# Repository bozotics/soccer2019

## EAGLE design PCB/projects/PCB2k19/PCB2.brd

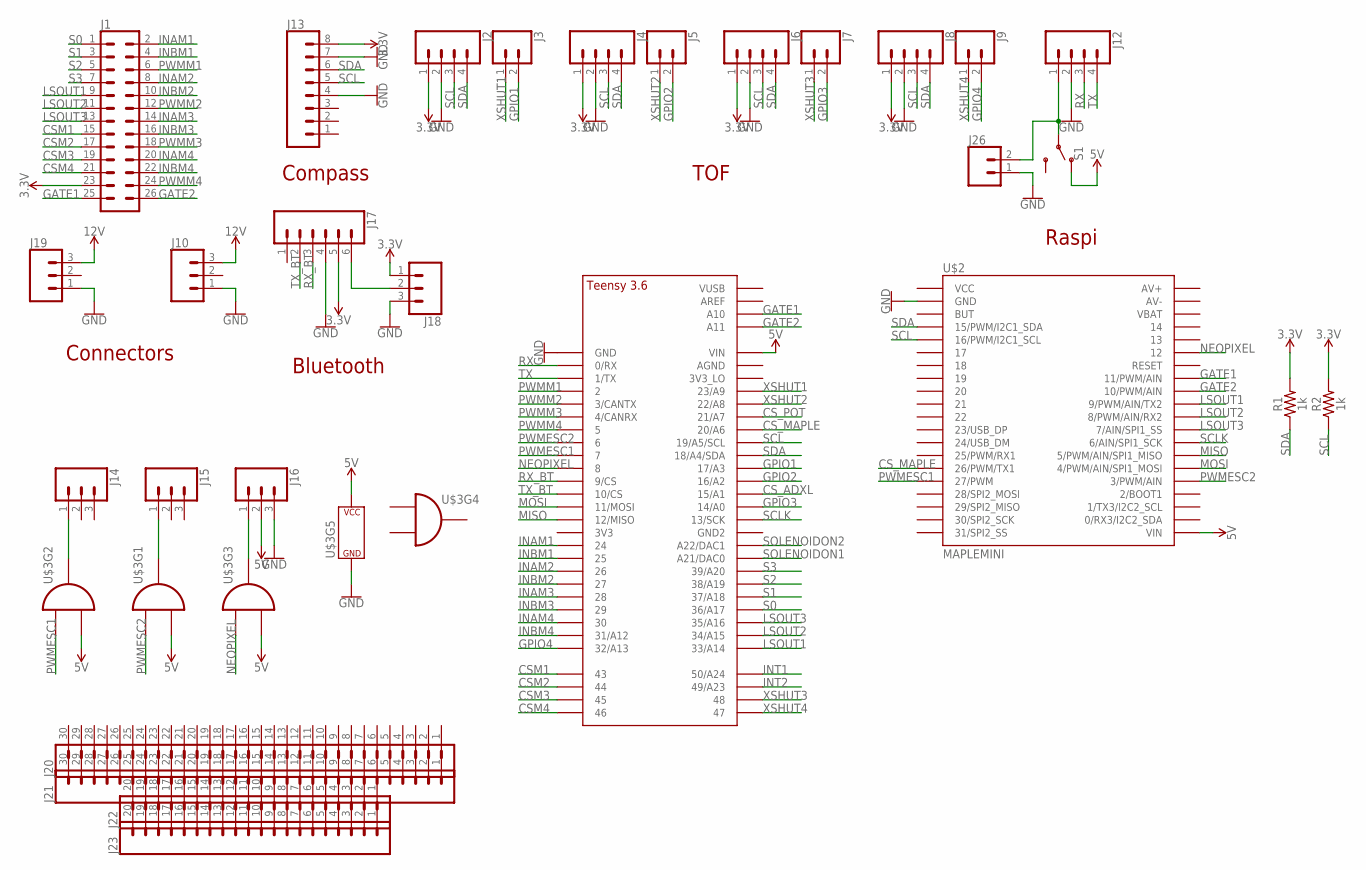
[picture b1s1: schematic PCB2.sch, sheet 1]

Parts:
J1: CONN_13X22X13; 2X13
J2, J4, J6, J8, J12: CONN_04LOCK; 1X04_LOCK
J3, J5, J7, J9, J26: CONN_02LOCK; 1X02_LOCK
J10, J19: CONN_03-SCREW-5MM; SCREWTERMINAL-5MM-3
J13: CONN_08LOCK; 1X08_LOCK
J14, J15, J16, J18: CONN_03LOCK; 1X03_LOCK
J17: CONN_06LOCK; 1X06_LOCK
J20, J21: CONN_30; 1X30
J22, J23: CONN_20; 1X20
R1, R2: 1k; 0603
S1: SWITCH-SPDT-PTH-11.6X4.0MM-LOCK; SWITCH_SPDT_PTH_11.6X4.0MM_LOCK
U$1: TEENSY_3.5/3.6_BASIC
U$2: MAPLEMINI; 20-DIP
U$3: 74HCT08; SOIC-14

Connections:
3.3V: J1.23, J2.1, J4.1, J6.1, J8.1, J13.8, J17.5, J18.1, R1.2, R2.2; also elsewhere on the board
5V: J16.2, S1.1 (O), U$1.VIN, U$2.21 (VIN), U$3.P2 (I1), U$3.P5 (I1), U$3.P10 (I1), U$3.P14 (P$V+); also elsewhere on the board
12V: J10.3, J19.3; also elsewhere on the board
CSM1: J1.15, U$1.43
CSM2: J1.17, U$1.44
CSM3: J1.19, U$1.45
CSM4: J1.21, U$1.46
CS_ADXL: U$1.15/A1; also elsewhere on the board
CS_MAPLE: U$1.20/A6, U$2.15 (26/PWM/TX1)
CS_POT: U$1.21/A7; also elsewhere on the board
GATE1: J1.25, U$1.A10, U$2.33 (11/PWM/AIN)
GATE2: J1.26, U$1.A11, U$2.32 (10/PWM/AIN)
GND: J2.2, J4.2, J6.2, J8.2, J10.1, J12.2, J13.4, J13.7, J16.3, J17.4, J18.3, J19.1, J26.1, U$1.GND, U$2.2 (GND), U$3.P7 (P$V-); also elsewhere on the board
GPIO1: J3.2, U$1.17/A3
GPIO2: J5.2, U$1.16/A2
GPIO3: J7.2, U$1.14/A0
GPIO4: J9.2, U$1.32/A13
INAM1: J1.2, U$1.24
INAM2: J1.8, U$1.26
INAM3: J1.14, U$1.28
INAM4: J1.20, U$1.30
INBM1: J1.4, U$1.25
INBM2: J1.10, U$1.27
INBM3: J1.16, U$1.29
INBM4: J1.22, U$1.31/A12
INT1: U$1.50/A24; also elsewhere on the board
INT2: U$1.49/A23; also elsewhere on the board
LSOUT1: J1.9, U$1.33/A14, U$2.31 (9/PWM/AIN/TX2)
LSOUT2: J1.11, U$1.34/A15, U$2.30 (8/PWM/AIN/RX2)
LSOUT3: J1.13, U$1.35/A16, U$2.29 (7/AIN/SPI1_SS)
MISO: U$1.12/MISO, U$2.27 (5/PWM/AIN/SPI1_MISO); also elsewhere on the board
MOSI: U$1.11/MOSI, U$2.26 (4/PWM/AIN/SPI1_MOSI); also elsewhere on the board
unnamed: J12.1, J26.2, S1.2
unnamed: J16.1, U$3.P8 (O)
unnamed: J14.1, U$3.P6 (O)
unnamed: J15.1, U$3.P3 (O)
unnamed: J17.6, J18.2
NEOPIXEL: U$1.8, U$2.35 (12), U$3.P9 (I0)
PWMESC1: U$1.7, U$2.16 (27/PWM), U$3.P4 (I0)
PWMESC2: U$1.6, U$2.25 (3/PWM/AIN), U$3.P1 (I0)
PWMM1: J1.6, U$1.2
PWMM2: J1.12, U$1.3/CANTX
PWMM3: J1.18, U$1.4/CANRX
PWMM4: J1.24, U$1.5
RX: J12.3, U$1.0/RX
RX_BT: J17.3, U$1.9/CS
S0: J1.1, U$1.36/A17
S1: J1.3, U$1.37/A18
S2: J1.5, U$1.38/A19
S3: J1.7, U$1.39/A20
SCL: J2.3, J4.3, J6.3, J8.3, J13.5, R2.1, U$1.19/A5/SCL, U$2.5 (16/PWM/I2C1_SCL)
SCLK: U$1.13/SCK, U$2.28 (6/AIN/SPI1_SCK); also elsewhere on the board
SDA: J2.4, J4.4, J6.4, J8.4, J13.6, R1.1, U$1.18/A4/SDA, U$2.4 (15/PWM/I2C1_SDA)
SOLENOIDON1: U$1.21/DAC0 (A21/DAC0); also elsewhere on the board
SOLENOIDON2: U$1.A22/DAC1; also elsewhere on the board
TX: J12.4, U$1.1/TX
TX_BT: J17.2, U$1.10/CS
XSHUT1: J3.1, U$1.23/A9
XSHUT2: J5.1, U$1.22/A8
XSHUT3: J7.1, U$1.48
XSHUT4: J9.1, U$1.47

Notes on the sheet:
Raspi
TOF
Compass
Connectors
Bluetooth

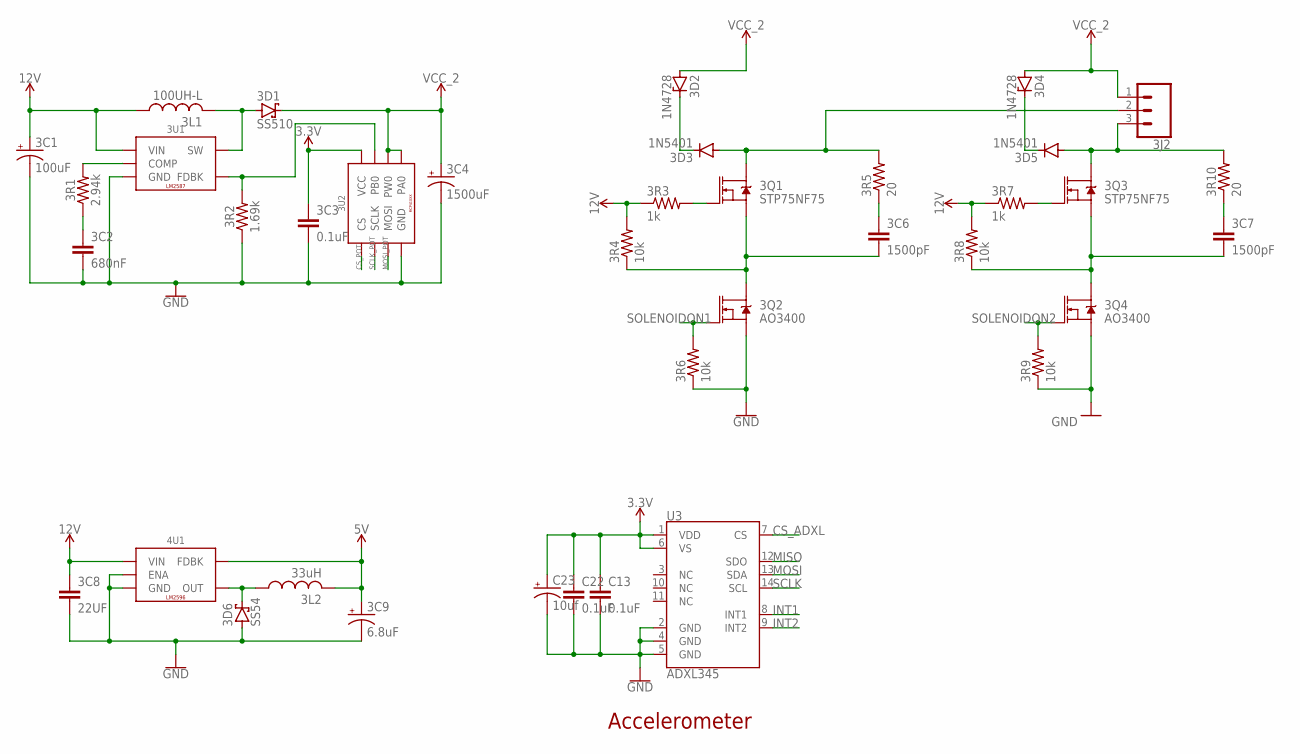
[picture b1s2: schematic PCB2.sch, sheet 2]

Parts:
3C1: 100uF; PANASONIC_D
3C2: 680nF; 0603
3C3: 0.1uF; 0603
3C4: 1500uF; 1000UF-CAP
3C6, 3C7: 1500pF; 0603
3C8: 22UF; 1210
3C9: 6.8uF; A/3216-18R
3D1: SS510; SMB
3D2, 3D4: 1N4728; DO41Z10
3D3, 3D5: 1N5401; DO201-15
3D6: SS54; SMB
3J2: CONN_03-SCREW-5MM; SCREWTERMINAL-5MM-3
3L1: 100UH-L
3L2: 33uH; 127
3Q1, 3Q3: STP75NF75; TO220V
3Q2, 3Q4: AO3400; SOT23-3
3R1: 2.94k; 0603
3R2: 1.69k; 0603
3R3, 3R7: 1k; 0603
3R4, 3R6, 3R8, 3R9: 10k; 0603
3R5, 3R10: 20; 0603
3U1: LM2587; TO-263
3U2: MCP41XXX; SOIC-8
4U1: LM2596; TO-263
C13, C22: 0.1uF; 0603
C23: 10uf; R/2012-12R
U3: ADXL345; LGA-14

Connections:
3.3V: 3C3.1, 3U2.8 (VCC), C13.1, C22.1, C23.+, U3.1 (VDD), U3.6 (VS); also elsewhere on the board
5V: 3C9.+, 3L2.2, 4U1.P4 (FDBK); also elsewhere on the board
12V: 3C1.+, 3C8.1, 3L1.P1 (1), 3R3.1, 3R4.2, 3R7.1, 3R8.2, 3U1.P5 (VIN), 4U1.P1 (VIN); also elsewhere on the board
CS_ADXL: U3.7 (CS); also elsewhere on the board
CS_POT: 3U2.1 (CS); also elsewhere on the board
GND: 3C1.-, 3C2.2, 3C3.2, 3C4.-, 3C8.2, 3C9.-, 3D6.A, 3Q2.2 (S), 3Q4.2 (S), 3R2.1, 3R6.1, 3R9.1, 3U1.P3 (GND), 3U2.4 (GND), 4U1.P3 (GND), 4U1.P5 (ENA), 4U1.TAB (GND), C13.2, C22.2, C23.-, U3.2 (GND), U3.4 (GND), U3.5 (GND); also elsewhere on the board
INT1: U3.8 (INT1); also elsewhere on the board
INT2: U3.9 (INT2); also elsewhere on the board
MISO: U3.12 (SDO); also elsewhere on the board
MOSI: U3.13 (SDA); also elsewhere on the board
MOSI_POT: 3U2.3 (MOSI)
unnamed: 3D1.A, 3L1.P2 (2), 3U1.P4 (SW)
unnamed: 3C6.2, 3Q1.3 (S), 3Q2.3 (D), 3R4.1
unnamed: 3R1.2, 3U1.P1 (COMP)
unnamed: 3C2.1, 3R1.1
unnamed: 3Q1.1 (G), 3R3.2
unnamed: 3D2.C, 3D3.C
unnamed: 3C6.1, 3R5.1
unnamed: 3C7.2, 3Q3.3 (S), 3Q4.3 (D), 3R8.1
unnamed: 3Q3.1 (G), 3R7.2
unnamed: 3D4.C, 3D5.C
unnamed: 3C7.1, 3R10.1
unnamed: 3D6.C, 3L2.1, 4U1.P2 (OUT)
unnamed: 3R2.2, 3U1.P2 (FDBK), 3U2.7 (PB0)
SCLK: U3.14 (SCL); also elsewhere on the board
SCLK_POT: 3U2.2 (SCLK)
SOLENOID-: 3D3.A, 3J2.2, 3Q1.2 (D), 3R5.2
SOLENOID-1: 3D5.A, 3J2.3, 3Q3.2 (D), 3R10.2
SOLENOIDON1: 3Q2.1 (G), 3R6.2; also elsewhere on the board
SOLENOIDON2: 3Q4.1 (G), 3R9.2; also elsewhere on the board
VCC_2: 3C4.+, 3D1.C, 3D2.A, 3D4.A, 3J2.1, 3U2.5 (PA0), 3U2.6 (PW0)

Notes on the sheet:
Accelerometer

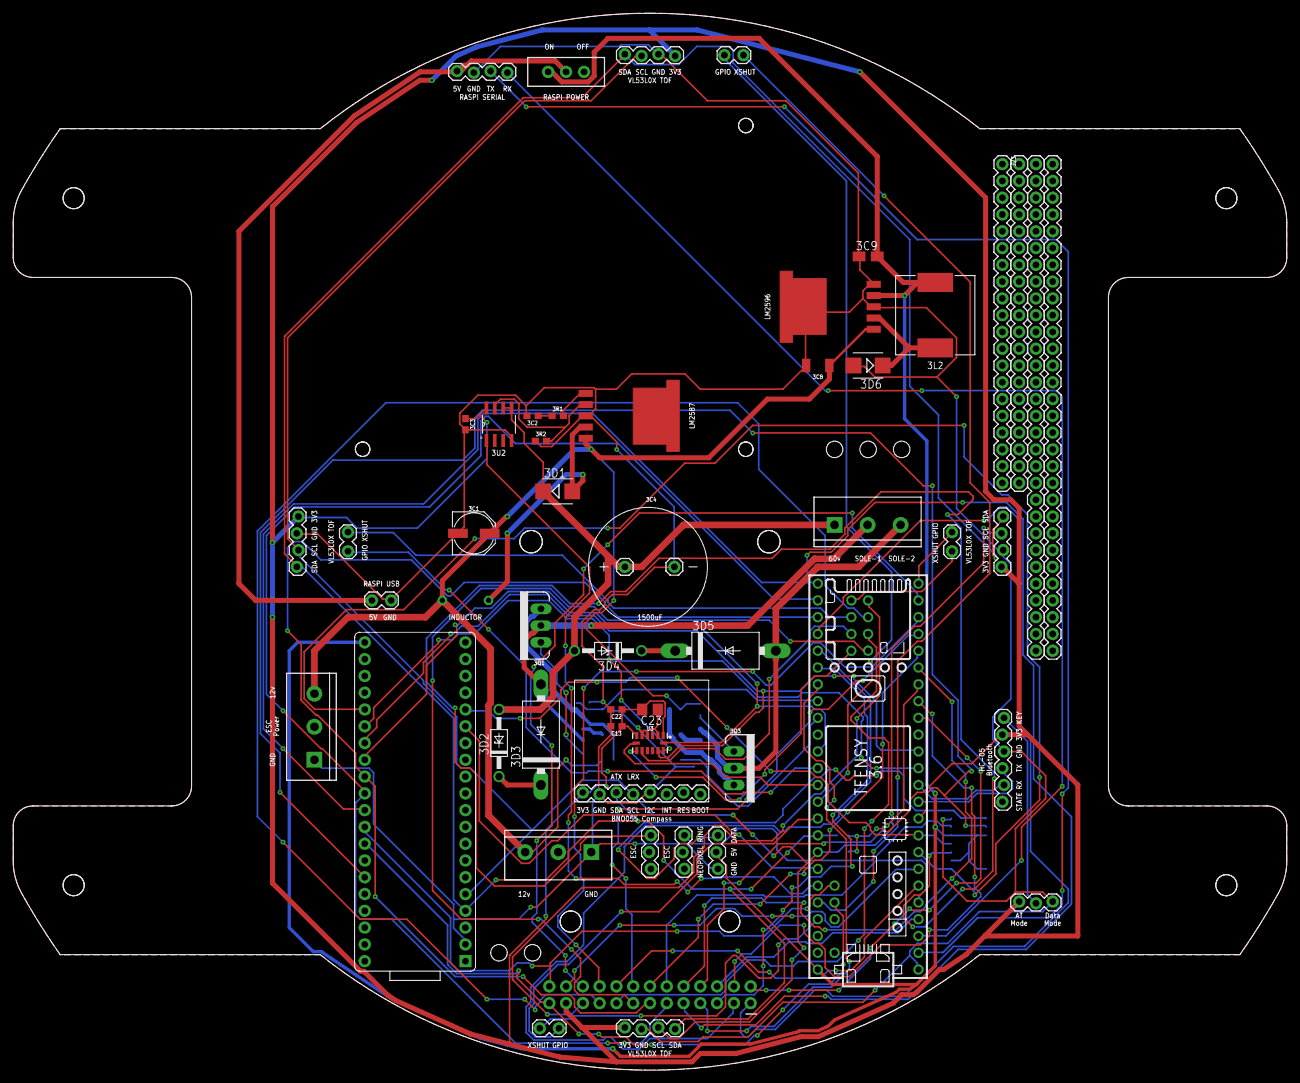
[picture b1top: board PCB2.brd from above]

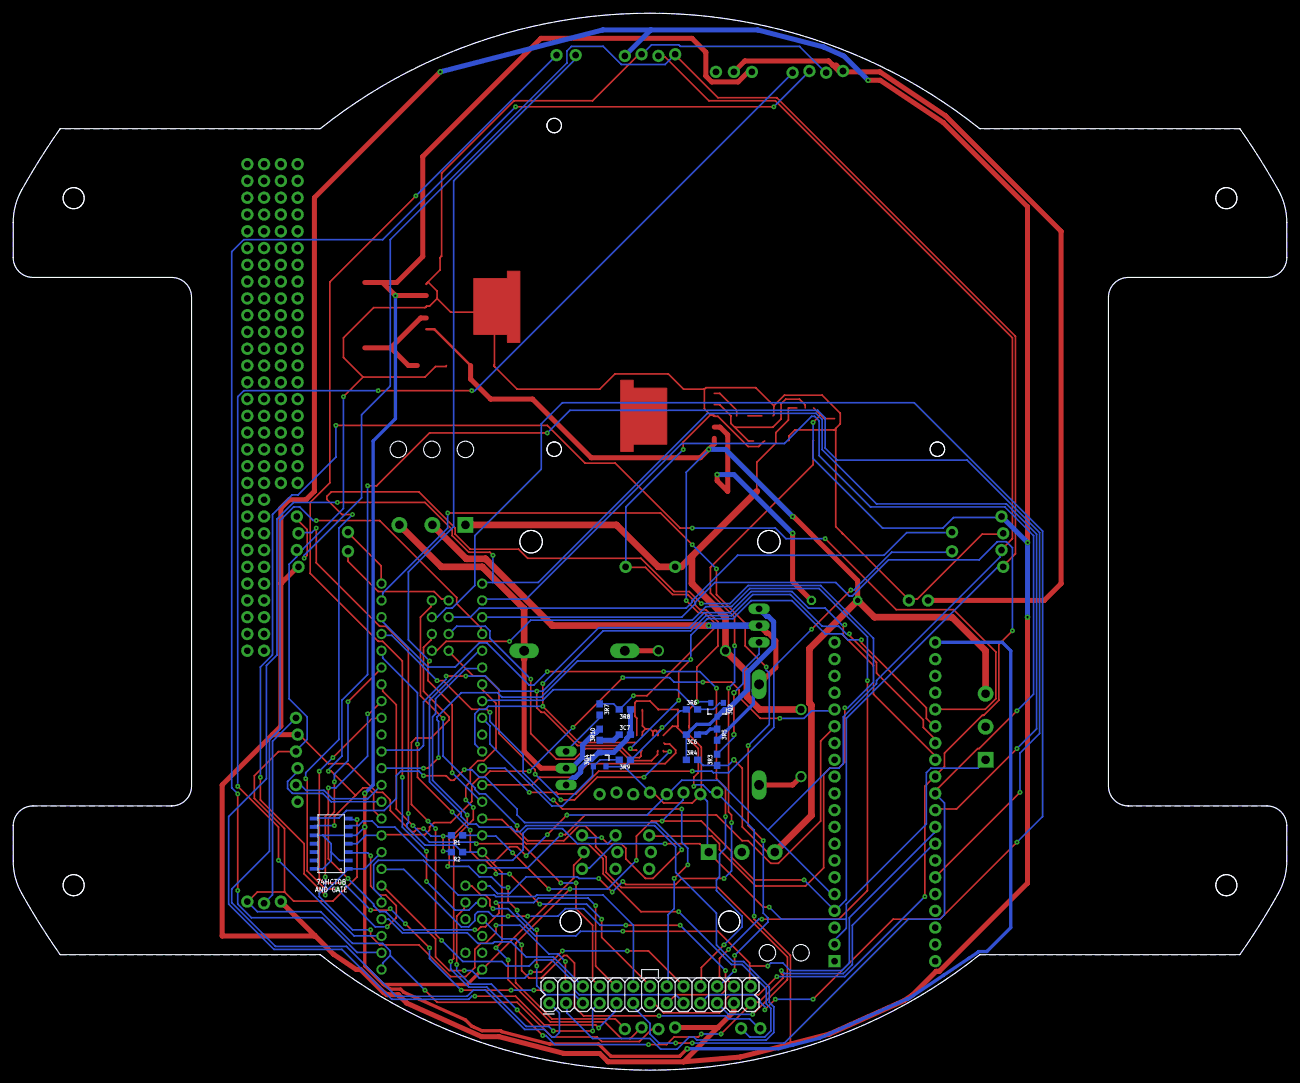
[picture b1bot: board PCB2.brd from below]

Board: 2 copper layers, 192.8 x 160.0 mm, 67 parts (16 on the bottom side), 77 nets.

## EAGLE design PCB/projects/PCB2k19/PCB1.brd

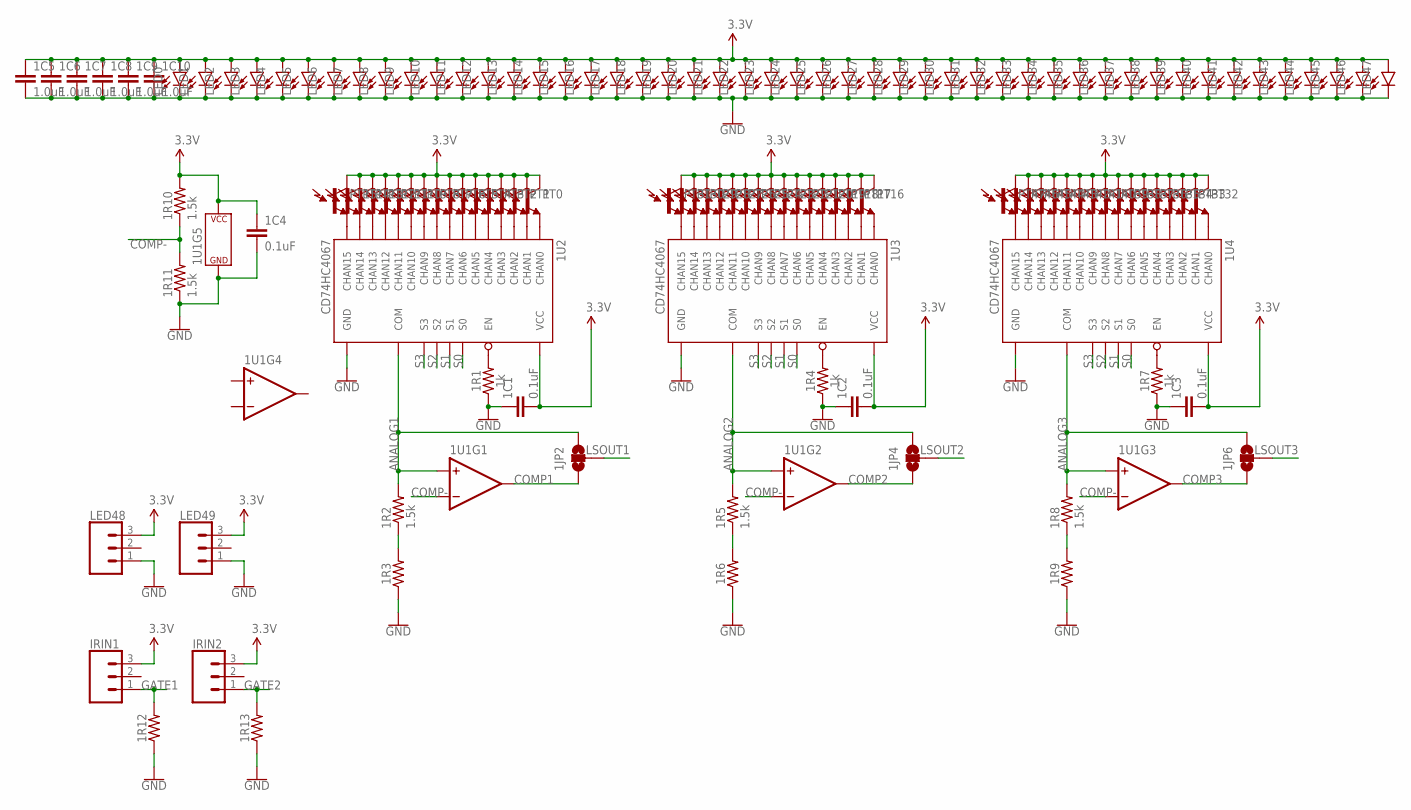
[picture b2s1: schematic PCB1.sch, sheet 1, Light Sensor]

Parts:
1C1, 1C2, 1C3, 1C4: 0.1uF; 0603
1C5, 1C6, 1C7, 1C8, 1C9, 1C10: 1.0uF; 0603
1JP2, 1JP4, 1JP6: JUMPER-SMT_3_NO_NO_SILK; SMT-JUMPER_3_0-NO_TRACE_NO-SILK
1R1, 1R4, 1R7: 1k; 0603
1R2, 1R5, 1R8, 1R10, 1R11: 1.5k; 0603
1R3, 1R6, 1R9, 1R12, 1R13: 0603
1U1: LM339; SOIC-14
1U2, 1U3, 1U4: CD74HC4067; SOIC-24
IRIN1, IRIN2: CONN_03; 1X03
LED0, LED1, LED2, LED3, LED4, LED5, LED6, LED7, LED8, LED9, LED10, LED11, LED12, LED13, LED14, LED15, LED16, LED17, LED18, LED19, LED20, LED21, LED22, LED23, LED24, LED25, LED26, LED27, LED28, LED29, LED30, LED31, LED32, LED33, LED34, LED35, LED36, LED37, LED38, LED39, LED40, LED41, LED42, LED43, LED44, LED45, LED46, LED47: 3528LED; 3528
LED48, LED49: CONN_03; 1X03
PT0, PT1, PT2, PT3, PT4, PT5, PT6, PT7, PT8, PT9, PT10, PT11, PT12, PT13, PT14, PT15, PT16, PT17, PT18, PT19, PT20, PT21, PT22, PT23, PT24, PT25, PT26, PT27, PT28, PT29, PT30, PT31, PT32, PT33, PT34, PT35, PT36, PT37, PT38, PT39, PT40, PT41, PT42, PT43, PT44, PT45, PT46, PT47: TEMT6000

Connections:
3.3V: 1C1.2, 1C2.2, 1C3.2, 1C4.1, 1C5.1, 1C6.1, 1C7.1, 1C8.1, 1C9.1, 1C10.1, 1R10.2, 1U1.P3 (P$V+), 1U2.P24 (VCC), 1U3.P24 (VCC), 1U4.P24 (VCC), IRIN1.3, IRIN2.3, LED0.A, LED1.A, LED2.A, LED3.A, LED4.A, LED5.A, LED6.A, LED7.A, LED8.A, LED9.A, LED10.A, LED11.A, LED12.A, LED13.A, LED14.A, LED15.A, LED16.A, LED17.A, LED18.A, LED19.A, LED20.A, LED21.A, LED22.A, LED23.A, LED24.A, LED25.A, LED26.A, LED27.A, LED28.A, LED29.A, LED30.A, LED31.A, LED32.A, LED33.A, LED34.A, LED35.A, LED36.A, LED37.A, LED38.A, LED39.A, LED40.A, LED41.A, LED42.A, LED43.A, LED44.A, LED45.A, LED46.A, LED47.A, LED48.3, LED49.3, PT0.COLLECTOR (C1), PT1.COLLECTOR (C1), PT2.COLLECTOR (C1), PT3.COLLECTOR (C1), PT4.COLLECTOR (C1), PT5.COLLECTOR (C1), PT6.COLLECTOR (C1), PT7.COLLECTOR (C1), PT8.COLLECTOR (C1), PT9.COLLECTOR (C1), PT10.COLLECTOR (C1), PT11.COLLECTOR (C1), PT12.COLLECTOR (C1), PT13.COLLECTOR (C1), PT14.COLLECTOR (C1), PT15.COLLECTOR (C1), PT16.COLLECTOR (C1), PT17.COLLECTOR (C1), PT18.COLLECTOR (C1), PT19.COLLECTOR (C1), PT20.COLLECTOR (C1), PT21.COLLECTOR (C1), PT22.COLLECTOR (C1), PT23.COLLECTOR (C1), PT24.COLLECTOR (C1), PT25.COLLECTOR (C1), PT26.COLLECTOR (C1), PT27.COLLECTOR (C1), PT28.COLLECTOR (C1), PT29.COLLECTOR (C1), PT30.COLLECTOR (C1), PT31.COLLECTOR (C1), PT32.COLLECTOR (C1), PT33.COLLECTOR (C1), PT34.COLLECTOR (C1), PT35.COLLECTOR (C1), PT36.COLLECTOR (C1), PT37.COLLECTOR (C1), PT38.COLLECTOR (C1), PT39.COLLECTOR (C1), PT40.COLLECTOR (C1), PT41.COLLECTOR (C1), PT42.COLLECTOR (C1), PT43.COLLECTOR (C1), PT44.COLLECTOR (C1), PT45.COLLECTOR (C1), PT46.COLLECTOR (C1), PT47.COLLECTOR (C1); also elsewhere on the board
ANALOG1: 1JP2.3, 1R2.2, 1U1.P5 (+IN), 1U2.P1 (COM)
ANALOG2: 1JP4.3, 1R5.2, 1U1.P7 (+IN), 1U3.P1 (COM)
ANALOG3: 1JP6.3, 1R8.2, 1U1.P9 (+IN), 1U4.P1 (COM)
COMP1: 1JP2.1, 1U1.P2 (OUT)
COMP2: 1JP4.1, 1U1.P1 (OUT)
COMP3: 1JP6.1, 1U1.P14 (OUT)
COMP-: 1R10.1, 1R11.2, 1U1.P4 (-IN), 1U1.P6 (-IN), 1U1.P8 (-IN)
GATE1: 1R12.2, IRIN1.1; also elsewhere on the board
GATE2: 1R13.2, IRIN2.1; also elsewhere on the board
GND: 1C1.1, 1C2.1, 1C3.1, 1C4.2, 1C5.2, 1C6.2, 1C7.2, 1C8.2, 1C9.2, 1C10.2, 1R1.1, 1R3.1, 1R4.1, 1R6.1, 1R7.1, 1R9.1, 1R11.1, 1R12.1, 1R13.1, 1U1.P12 (P$V-), 1U2.P12 (GND), 1U3.P12 (GND), 1U4.P12 (GND), LED0.C, LED1.C, LED2.C, LED3.C, LED4.C, LED5.C, LED6.C, LED7.C, LED8.C, LED9.C, LED10.C, LED11.C, LED12.C, LED13.C, LED14.C, LED15.C, LED16.C, LED17.C, LED18.C, LED19.C, LED20.C, LED21.C, LED22.C, LED23.C, LED24.C, LED25.C, LED26.C, LED27.C, LED28.C, LED29.C, LED30.C, LED31.C, LED32.C, LED33.C, LED34.C, LED35.C, LED36.C, LED37.C, LED38.C, LED39.C, LED40.C, LED41.C, LED42.C, LED43.C, LED44.C, LED45.C, LED46.C, LED47.C, LED48.1, LED49.1; also elsewhere on the board
LSOUT1: 1JP2.2; also elsewhere on the board
LSOUT2: 1JP4.2; also elsewhere on the board
LSOUT3: 1JP6.2; also elsewhere on the board
unnamed: 1U2.P9 (CHAN0), PT0.EMITTER (E1)
unnamed: 1R1.2, 1U2.P15 (EN)
unnamed: 1U2.P8 (CHAN1), PT1.EMITTER (E1)
unnamed: 1U2.P7 (CHAN2), PT2.EMITTER (E1)
unnamed: 1U2.P6 (CHAN3), PT3.EMITTER (E1)
unnamed: 1U2.P5 (CHAN4), PT4.EMITTER (E1)
unnamed: 1U2.P4 (CHAN5), PT5.EMITTER (E1)
unnamed: 1U2.P3 (CHAN6), PT6.EMITTER (E1)
unnamed: 1U2.P2 (CHAN7), PT7.EMITTER (E1)
unnamed: 1U2.P23 (CHAN8), PT8.EMITTER (E1)
unnamed: 1U2.P22 (CHAN9), PT9.EMITTER (E1)
unnamed: 1U2.P21 (CHAN10), PT10.EMITTER (E1)
unnamed: 1U2.P20 (CHAN11), PT11.EMITTER (E1)
unnamed: 1U2.P19 (CHAN12), PT12.EMITTER (E1)
unnamed: 1U2.P18 (CHAN13), PT13.EMITTER (E1)
unnamed: 1U2.P17 (CHAN14), PT14.EMITTER (E1)
unnamed: 1U2.P16 (CHAN15), PT15.EMITTER (E1)
unnamed: 1R4.2, 1U3.P15 (EN)
unnamed: 1R2.1, 1R3.2
unnamed: 1U3.P9 (CHAN0), PT16.EMITTER (E1)
unnamed: 1U3.P8 (CHAN1), PT17.EMITTER (E1)
unnamed: 1R5.1, 1R6.2
unnamed: 1U3.P7 (CHAN2), PT18.EMITTER (E1)
unnamed: 1U3.P6 (CHAN3), PT19.EMITTER (E1)
unnamed: 1U3.P5 (CHAN4), PT20.EMITTER (E1)
unnamed: 1U3.P4 (CHAN5), PT21.EMITTER (E1)
unnamed: 1U3.P3 (CHAN6), PT22.EMITTER (E1)
unnamed: 1U3.P2 (CHAN7), PT23.EMITTER (E1)
unnamed: 1U3.P23 (CHAN8), PT24.EMITTER (E1)
unnamed: 1U3.P22 (CHAN9), PT25.EMITTER (E1)
unnamed: 1U3.P21 (CHAN10), PT26.EMITTER (E1)
unnamed: 1U3.P20 (CHAN11), PT27.EMITTER (E1)
unnamed: 1U3.P19 (CHAN12), PT28.EMITTER (E1)
unnamed: 1U3.P18 (CHAN13), PT29.EMITTER (E1)
unnamed: 1U3.P17 (CHAN14), PT30.EMITTER (E1)
unnamed: 1U3.P16 (CHAN15), PT31.EMITTER (E1)
unnamed: 1U4.P9 (CHAN0), PT32.EMITTER (E1)
unnamed: 1U4.P8 (CHAN1), PT33.EMITTER (E1)
unnamed: 1R7.2, 1U4.P15 (EN)
unnamed: 1R8.1, 1R9.2
unnamed: 1U4.P7 (CHAN2), PT34.EMITTER (E1)
unnamed: 1U4.P6 (CHAN3), PT35.EMITTER (E1)
unnamed: 1U4.P5 (CHAN4), PT36.EMITTER (E1)
unnamed: 1U4.P4 (CHAN5), PT37.EMITTER (E1)
unnamed: 1U4.P3 (CHAN6), PT38.EMITTER (E1)
unnamed: 1U4.P2 (CHAN7), PT39.EMITTER (E1)
unnamed: 1U4.P23 (CHAN8), PT40.EMITTER (E1)
unnamed: 1U4.P22 (CHAN9), PT41.EMITTER (E1)
unnamed: 1U4.P21 (CHAN10), PT42.EMITTER (E1)
unnamed: 1U4.P20 (CHAN11), PT43.EMITTER (E1)
unnamed: 1U4.P19 (CHAN12), PT44.EMITTER (E1)
unnamed: 1U4.P18 (CHAN13), PT45.EMITTER (E1)
unnamed: 1U4.P17 (CHAN14), PT46.EMITTER (E1)
unnamed: 1U4.P16 (CHAN15), PT47.EMITTER (E1)
S0: 1U2.P10 (S0), 1U3.P10 (S0), 1U4.P10 (S0); also elsewhere on the board
S1: 1U2.P11 (S1), 1U3.P11 (S1), 1U4.P11 (S1); also elsewhere on the board
S2: 1U2.P14 (S2), 1U3.P14 (S2), 1U4.P14 (S2); also elsewhere on the board
S3: 1U2.P13 (S3), 1U3.P13 (S3), 1U4.P13 (S3); also elsewhere on the board

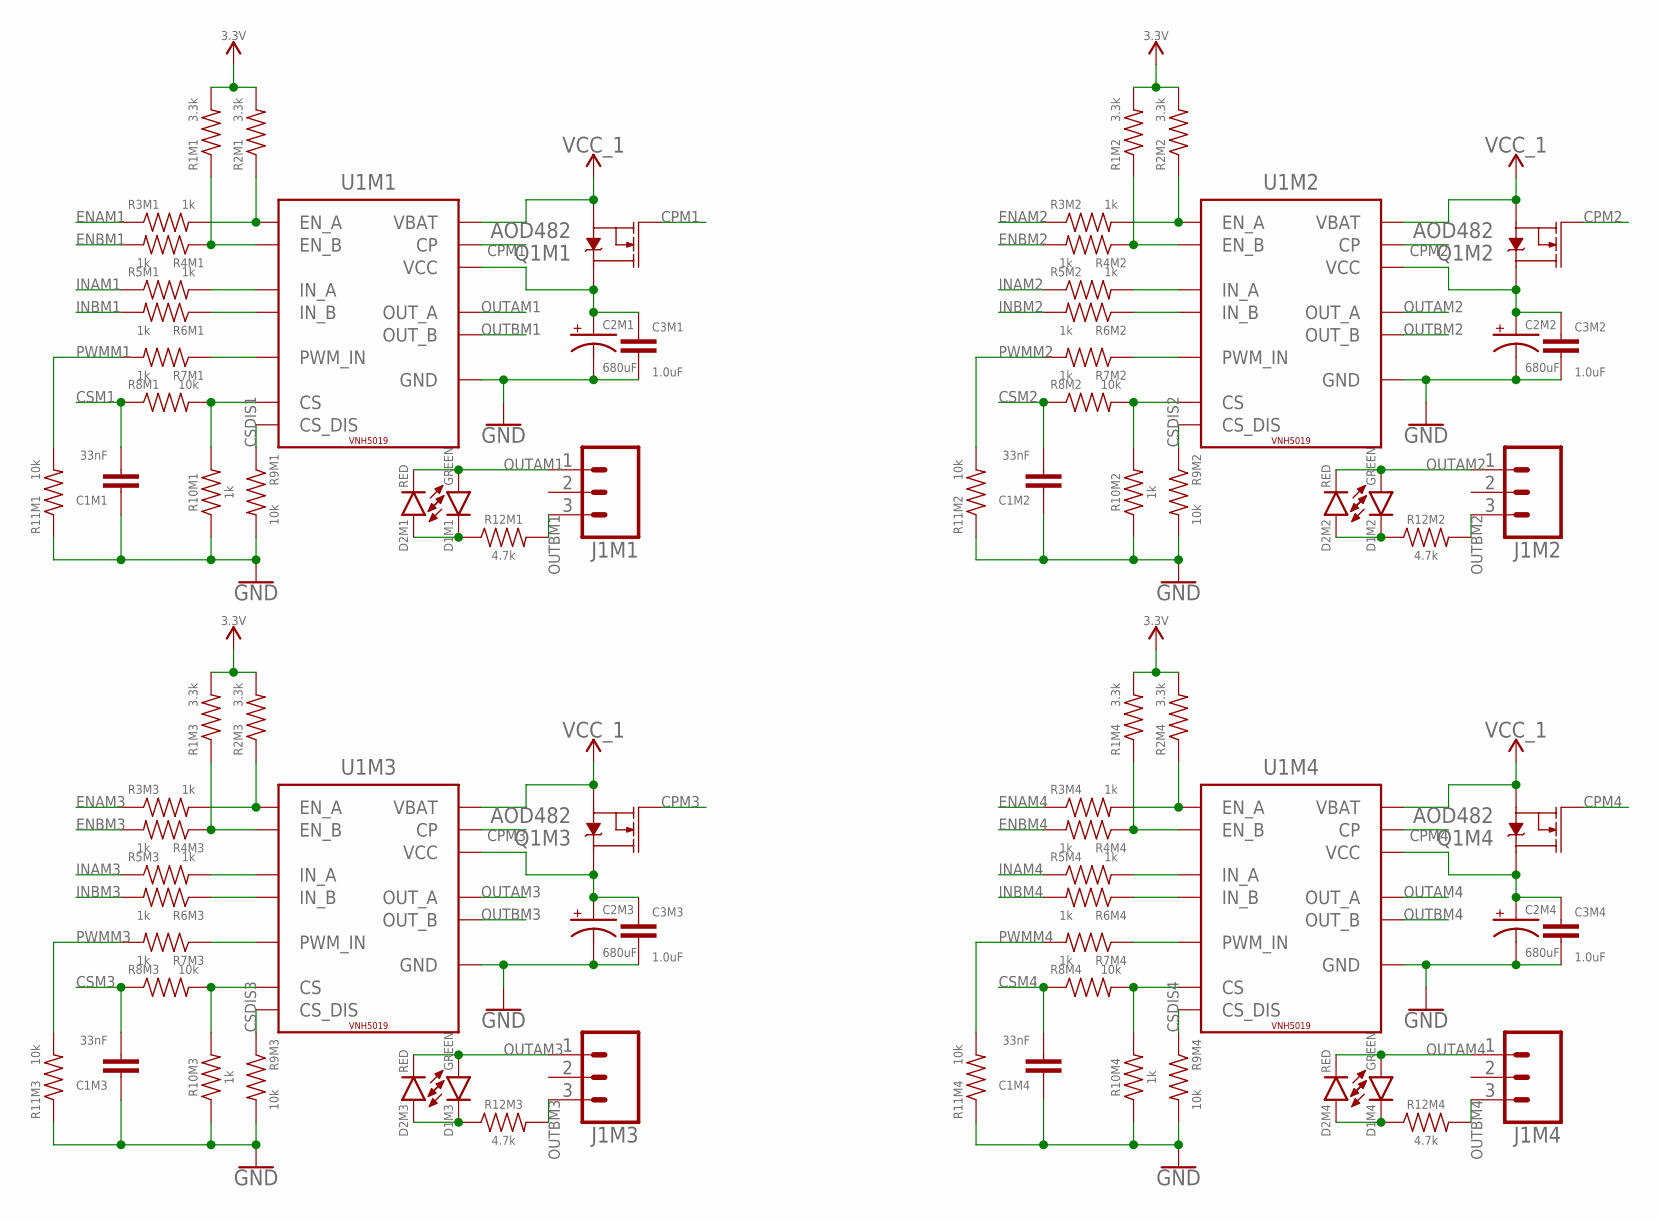
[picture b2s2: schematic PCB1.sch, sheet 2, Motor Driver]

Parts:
C1M1, C1M2, C1M3, C1M4: 33nF; 0603
C2M1, C2M2, C2M3, C2M4: 680uF; E3,5-8
C3M1, C3M2, C3M3, C3M4: 1.0uF; 0603
D1M1, D1M2, D1M3, D1M4: GREEN; LED-0603
D2M1, D2M2, D2M3, D2M4: RED; LED-0603
J1M1, J1M2, J1M3, J1M4: CONN_03-SCREW-5MM; SCREWTERMINAL-5MM-3
Q1M1, Q1M2, Q1M3, Q1M4: AOD482; DPAK
R1M1, R1M2, R1M3, R1M4, R2M1, R2M2, R2M3, R2M4: 3.3k; 0603
R3M1, R3M2, R3M3, R3M4, R4M1, R4M2, R4M3, R4M4, R5M1, R5M2, R5M3, R5M4, R6M1, R6M2, R6M3, R6M4, R7M1, R7M2, R7M3, R7M4, R10M1, R10M2, R10M3, R10M4: 1k; 0603
R8M1, R8M2, R8M3, R8M4, R9M1, R9M2, R9M3, R9M4, R11M1, R11M2, R11M3, R11M4: 10k; 0603
R12M1, R12M2, R12M3, R12M4: 4.7k; 0603
U1M1, U1M2, U1M3, U1M4: VNH5019; POWERSO-30

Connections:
3.3V: R1M1.2, R1M2.2, R1M3.2, R1M4.2, R2M1.2, R2M2.2, R2M3.2, R2M4.2; also elsewhere on the board
CPM1: Q1M1.1 (G), U1M1.P11 (CP)
CPM2: Q1M2.1 (G), U1M2.P11 (CP)
CPM3: Q1M3.1 (G), U1M3.P11 (CP)
CPM4: Q1M4.1 (G), U1M4.P11 (CP)
CSDIS1: R9M1.1, U1M1.P6 (CS_DIS)
CSDIS2: R9M2.1, U1M2.P6 (CS_DIS)
CSDIS3: R9M3.1, U1M3.P6 (CS_DIS)
CSDIS4: R9M4.1, U1M4.P6 (CS_DIS)
CSM1: C1M1.2, R8M1.1; also elsewhere on the board
CSM2: C1M2.2, R8M2.1; also elsewhere on the board
CSM3: C1M3.2, R8M3.1; also elsewhere on the board
CSM4: C1M4.2, R8M4.1; also elsewhere on the board
ENAM1: R3M1.1
ENAM2: R3M2.1
ENAM3: R3M3.1
ENAM4: R3M4.1
ENBM1: R4M1.2
ENBM2: R4M2.2
ENBM3: R4M3.2
ENBM4: R4M4.2
GND: C1M1.1, C1M2.1, C1M3.1, C1M4.1, C2M1.-, C2M2.-, C2M3.-, C2M4.-, C3M1.2, C3M2.2, C3M3.2, C3M4.2, R9M1.2, R9M2.2, R9M3.2, R9M4.2, R10M1.1, R10M2.1, R10M3.1, R10M4.1, R11M1.1, R11M2.1, R11M3.1, R11M4.1, U1M1.P18 (GND), U1M1.P19 (GND), U1M1.P20 (GND), U1M1.P26 (GND), U1M1.P27 (GND), U1M1.P28 (GND), U1M2.P18 (GND), U1M2.P19 (GND), U1M2.P20 (GND), U1M2.P26 (GND), U1M2.P27 (GND), U1M2.P28 (GND), U1M3.P18 (GND), U1M3.P19 (GND), U1M3.P20 (GND), U1M3.P26 (GND), U1M3.P27 (GND), U1M3.P28 (GND), U1M4.P18 (GND), U1M4.P19 (GND), U1M4.P20 (GND), U1M4.P26 (GND), U1M4.P27 (GND), U1M4.P28 (GND); also elsewhere on the board
INAM1: R5M1.1; also elsewhere on the board
INAM2: R5M2.1; also elsewhere on the board
INAM3: R5M3.1; also elsewhere on the board
INAM4: R5M4.1; also elsewhere on the board
INBM1: R6M1.2; also elsewhere on the board
INBM2: R6M2.2; also elsewhere on the board
INBM3: R6M3.2; also elsewhere on the board
INBM4: R6M4.2; also elsewhere on the board
unnamed: R2M1.1, R3M1.2, U1M1.P5 (EN_A)
unnamed: C2M1.+, C3M1.1, Q1M1.4 (D), U1M1.P3 (VCC), U1M1.P13 (VCC), U1M1.P23 (VCC), U1M1.SLUG1 (VCC)
unnamed: R1M1.1, R4M1.1, U1M1.P9 (EN_B)
unnamed: R6M1.1, U1M1.P10 (IN_B)
unnamed: R5M1.2, U1M1.P4 (IN_A)
unnamed: R8M1.2, R10M1.2, U1M1.P8 (CS)
unnamed: R7M1.1, U1M1.P7 (PWM_IN)
unnamed: C2M2.+, C3M2.1, Q1M2.4 (D), U1M2.P3 (VCC), U1M2.P13 (VCC), U1M2.P23 (VCC), U1M2.SLUG1 (VCC)
unnamed: R2M2.1, R3M2.2, U1M2.P5 (EN_A)
unnamed: R5M2.2, U1M2.P4 (IN_A)
unnamed: D1M1.C, D2M1.A, R12M1.1
unnamed: R1M2.1, R4M2.1, U1M2.P9 (EN_B)
unnamed: R6M2.1, U1M2.P10 (IN_B)
unnamed: R8M2.2, R10M2.2, U1M2.P8 (CS)
unnamed: R7M2.1, U1M2.P7 (PWM_IN)
unnamed: D1M2.C, D2M2.A, R12M2.1
unnamed: C2M3.+, C3M3.1, Q1M3.4 (D), U1M3.P3 (VCC), U1M3.P13 (VCC), U1M3.P23 (VCC), U1M3.SLUG1 (VCC)
unnamed: R2M3.1, R3M3.2, U1M3.P5 (EN_A)
unnamed: R5M3.2, U1M3.P4 (IN_A)
unnamed: R1M3.1, R4M3.1, U1M3.P9 (EN_B)
unnamed: R6M3.1, U1M3.P10 (IN_B)
unnamed: R8M3.2, R10M3.2, U1M3.P8 (CS)
unnamed: R7M3.1, U1M3.P7 (PWM_IN)
unnamed: D1M3.C, D2M3.A, R12M3.1
unnamed: C2M4.+, C3M4.1, Q1M4.4 (D), U1M4.P3 (VCC), U1M4.P13 (VCC), U1M4.P23 (VCC), U1M4.SLUG1 (VCC)
unnamed: R2M4.1, R3M4.2, U1M4.P5 (EN_A)
unnamed: R5M4.2, U1M4.P4 (IN_A)
unnamed: R1M4.1, R4M4.1, U1M4.P9 (EN_B)
unnamed: R6M4.1, U1M4.P10 (IN_B)
unnamed: R8M4.2, R10M4.2, U1M4.P8 (CS)
unnamed: R7M4.1, U1M4.P7 (PWM_IN)
unnamed: D1M4.C, D2M4.A, R12M4.1
OUTAM1: D1M1.A, D2M1.C, J1M1.1, U1M1.P1 (OUT_A), U1M1.P25 (OUT_A), U1M1.P30 (OUT_A), U1M1.SLUG2 (OUT_A)
OUTAM2: D1M2.A, D2M2.C, J1M2.1, U1M2.P1 (OUT_A), U1M2.P25 (OUT_A), U1M2.P30 (OUT_A), U1M2.SLUG2 (OUT_A)
OUTAM3: D1M3.A, D2M3.C, J1M3.1, U1M3.P1 (OUT_A), U1M3.P25 (OUT_A), U1M3.P30 (OUT_A), U1M3.SLUG2 (OUT_A)
OUTAM4: D1M4.A, D2M4.C, J1M4.1, U1M4.P1 (OUT_A), U1M4.P25 (OUT_A), U1M4.P30 (OUT_A), U1M4.SLUG2 (OUT_A)
OUTBM1: J1M1.3, R12M1.2, U1M1.P15 (OUT_B), U1M1.P16 (OUT_B), U1M1.P21 (OUT_B), U1M1.SLUG3 (OUT_B)
OUTBM2: J1M2.3, R12M2.2, U1M2.P15 (OUT_B), U1M2.P16 (OUT_B), U1M2.P21 (OUT_B), U1M2.SLUG3 (OUT_B)
OUTBM3: J1M3.3, R12M3.2, U1M3.P15 (OUT_B), U1M3.P16 (OUT_B), U1M3.P21 (OUT_B), U1M3.SLUG3 (OUT_B)
OUTBM4: J1M4.3, R12M4.2, U1M4.P15 (OUT_B), U1M4.P16 (OUT_B), U1M4.P21 (OUT_B), U1M4.SLUG3 (OUT_B)
PWMM1: R7M1.2, R11M1.2; also elsewhere on the board
PWMM2: R7M2.2, R11M2.2; also elsewhere on the board
PWMM3: R7M3.2, R11M3.2; also elsewhere on the board
PWMM4: R7M4.2, R11M4.2; also elsewhere on the board
VCC_1: Q1M1.3 (S), Q1M2.3 (S), Q1M3.3 (S), Q1M4.3 (S), U1M1.P12 (VBAT), U1M2.P12 (VBAT), U1M3.P12 (VBAT), U1M4.P12 (VBAT); also elsewhere on the board

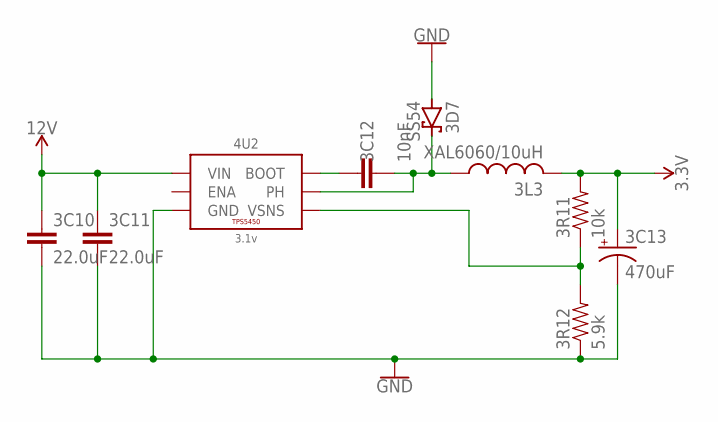
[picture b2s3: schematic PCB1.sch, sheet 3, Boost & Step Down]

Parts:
3C10, 3C11: 22.0uF; 1210
3C12: 10nF; 0603
3C13: 470uF; D/7343-31R
3D7: SS54; SMB
3L3: XAL6060/10uH; XAL6060
3R11: 10k; 0603
3R12: 5.9k; 0603
4U2: 3.1v; POWERPAD-SOIC-8

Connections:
3.3V: 3C13.+, 3L3.2, 3R11.2; also elsewhere on the board
12V: 3C10.1, 3C11.1, 4U2.7 (VIN); also elsewhere on the board
GND: 3C10.2, 3C11.2, 3C13.-, 3D7.A, 3R12.1, 4U2.6 (GND), 4U2.9 (GND), 4U2.P$1 (GND), 4U2.P$2 (GND), 4U2.P$3 (GND), 4U2.P$4 (GND), 4U2.P$5 (GND), 4U2.P$6 (GND); also elsewhere on the board
unnamed: 3C12.1, 4U2.1 (BOOT)
unnamed: 3C12.2, 3D7.C, 3L3.1, 4U2.8 (PH)
unnamed: 3R11.1, 3R12.2, 4U2.4 (VSNS)

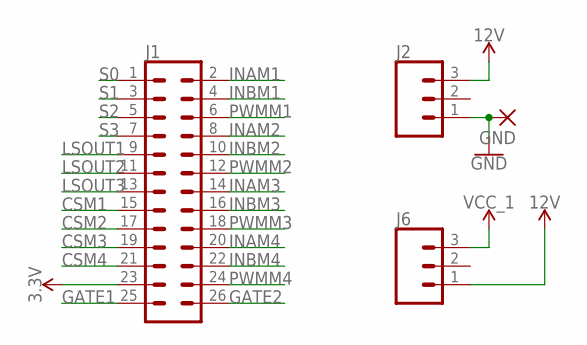
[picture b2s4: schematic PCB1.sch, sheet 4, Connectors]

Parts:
GND: 3,17/1,1
J1: CONN_13X22X13; 2X13
J2, J6: CONN_03-SCREW-5MM; SCREWTERMINAL-5MM-3

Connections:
3.3V: J1.23; also elsewhere on the board
12V: J2.3, J6.1; also elsewhere on the board
CSM1: J1.15; also elsewhere on the board
CSM2: J1.17; also elsewhere on the board
CSM3: J1.19; also elsewhere on the board
CSM4: J1.21; also elsewhere on the board
GATE1: J1.25; also elsewhere on the board
GATE2: J1.26; also elsewhere on the board
GND: GND.1, J2.1; also elsewhere on the board
INAM1: J1.2; also elsewhere on the board
INAM2: J1.8; also elsewhere on the board
INAM3: J1.14; also elsewhere on the board
INAM4: J1.20; also elsewhere on the board
INBM1: J1.4; also elsewhere on the board
INBM2: J1.10; also elsewhere on the board
INBM3: J1.16; also elsewhere on the board
INBM4: J1.22; also elsewhere on the board
LSOUT1: J1.9; also elsewhere on the board
LSOUT2: J1.11; also elsewhere on the board
LSOUT3: J1.13; also elsewhere on the board
PWMM1: J1.6; also elsewhere on the board
PWMM2: J1.12; also elsewhere on the board
PWMM3: J1.18; also elsewhere on the board
PWMM4: J1.24; also elsewhere on the board
S0: J1.1; also elsewhere on the board
S1: J1.3; also elsewhere on the board
S2: J1.5; also elsewhere on the board
S3: J1.7; also elsewhere on the board
VCC_1: J6.3; also elsewhere on the board

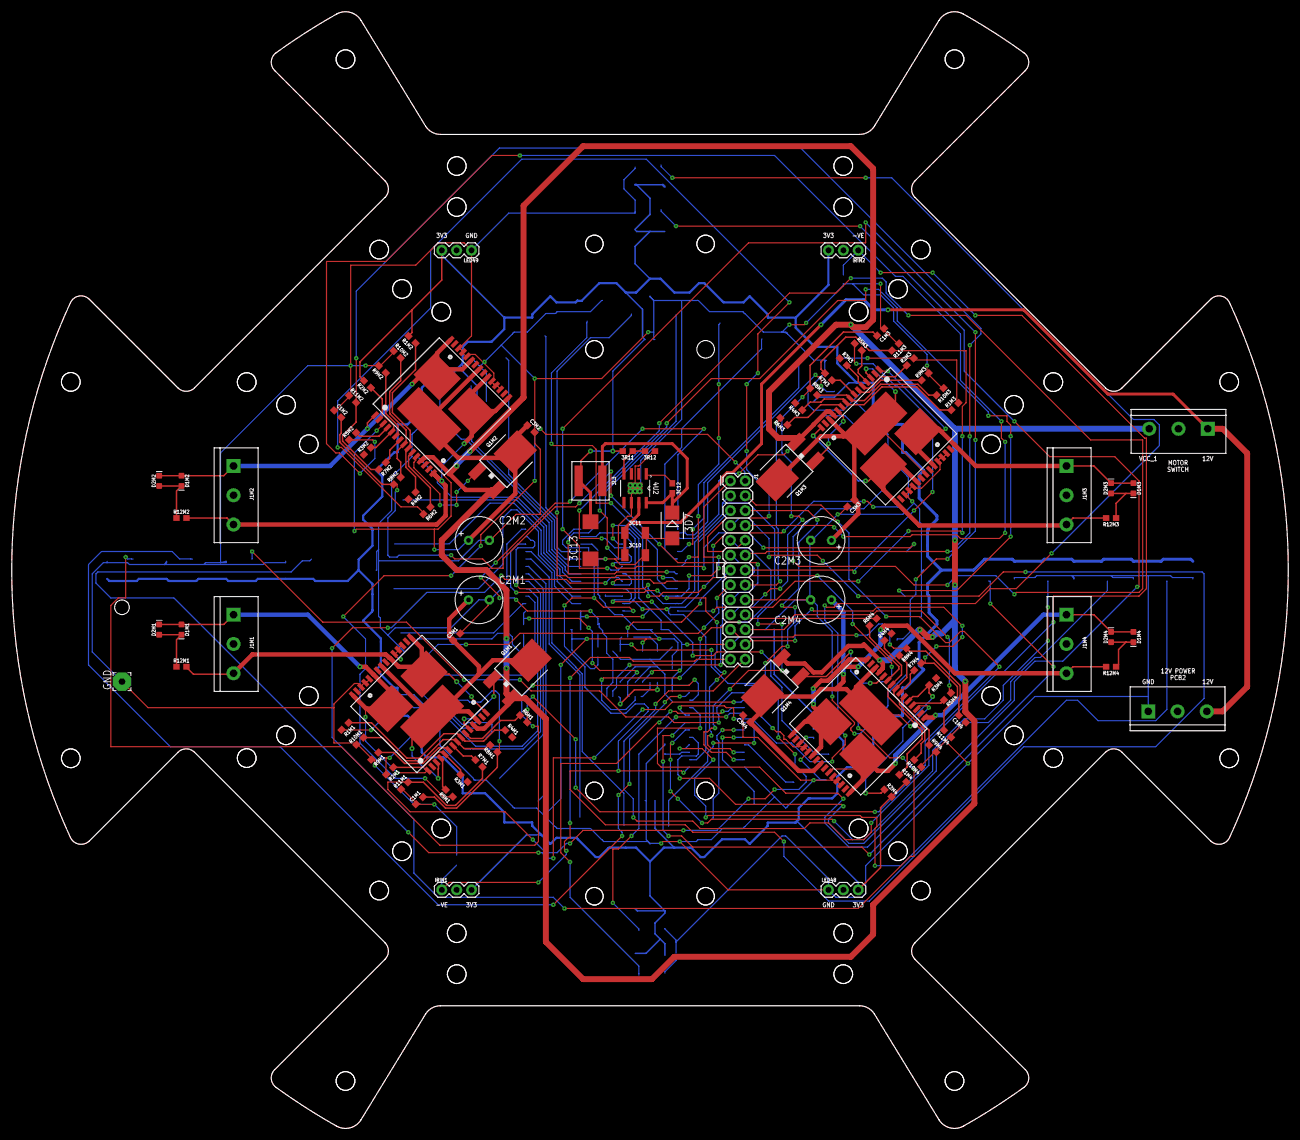
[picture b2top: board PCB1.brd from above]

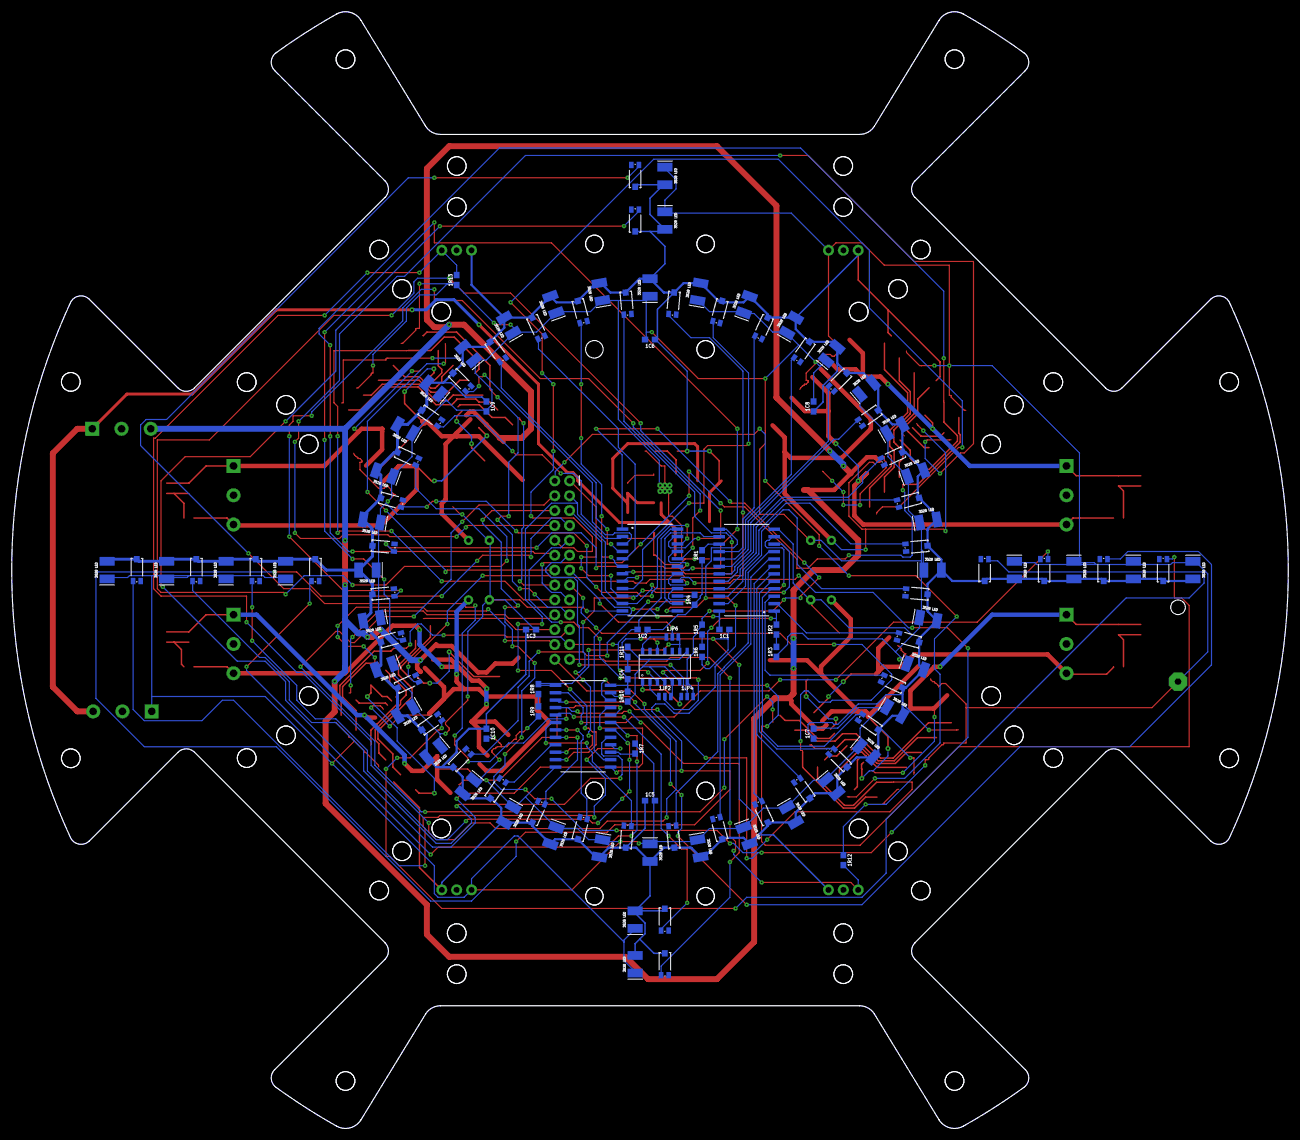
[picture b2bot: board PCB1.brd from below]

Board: 2 copper layers, 218.0 x 190.7 mm, 223 parts (126 on the bottom side), 141 nets.

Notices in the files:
parts and their libraries:
SparkFun-Sensors: Licensing: Creative Commons ShareAlike 4.0 International - https://creativecommons.org/licenses/by-sa/4.0
